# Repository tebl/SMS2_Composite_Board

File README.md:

# Master System II Video Board

The Sega Master System II was launched in a newer and updated styled case, unfortunately also missing quite a few features that were found in its earlier incarnation. Chief among them was the video output option, forcing you to rely on RF - an option being dropped on most newer TVs as well as looking rather dreadful on those that still have it.

This board aims to add composite or S-video back to your favourite mark II, making it usable today and giving you back the fun you had back in the day! Probably won't need a board like this since there aren't all that many connections and components in the first place, but tried it out and when doing more than one system conversion I figured there was enough of a wire mess to deal with so a small board made sense.

Board is sectioned off so that only the top section is used for composite video, so if you don't intend to use s-video you can save a bunch of wireing and skip these components. Note that it is important to pick power and ground connections that are close to the CXA1145P chip, but not every source is equal - while both pin 12 and 19 are power pins, using 12 as VCC for the circuit will result in glitches on the system (mine goes B/W and flashes purple from time to time) so stick with 19 for that. Don't do what I did, count twice and solder it right the first time. See images below for inspiration!

The extra wires going to the 64-pin chip (leg is cut to make this work) is used in combination with the switch to toggle between 50 and 60Hz. In PAL consoles this is used to let us play the game at full speed, just like the japanese and american consoles. At this point I consider the stock 50Hz setting "easy"-mode!

# Schematic
The supplied KiCad files should be sufficient as both a schematic and as a  starting point for ordering PCBs (basically you could just zip the contents of the export folder and upload that on a fabrication site), the schematic is also available in [PDF-format](https://github.com/tebl/SMS2_Composite_Board/raw/master/export/Master%20System%20II%20Video%20Board.pdf) and this is what you'll need to print and work your way through this things don't work as expected after assembly.

# BOM
Most parts should be easy to get a hold of from your favourite local electronic component shop, but given that I don't have access to such shops where I live so everything was based on whatever I could get cheapest from ebay/AliExpress (free shipping, plan on usually waiting 3-4 weeks though). The list below should be everything you'll need in addition to a workable soldering iron and some 60/40 soldering tin. For superior results, consider using shielded wire when doing the install!

Components in parenthesis are those needed extra for the S-video parts, so feel free to only install the parts needed for your own setup.

| Reference    | Item                                  | Count |
| ------------ | ------------------------------------- | ----- |
| PCB          | Fabricate using Gerber files ([order](https://www.pcbway.com/project/shareproject/Sega_Master_System_II_Composite_Video_Board.html=88707))  |     1 |
| C1           | 470uf electrolytic capacitor          |     1 |
| R1           | 150 ohm resistor                      |   (1) | 
| R2,R4        | 75 ohm resistor                       |     2 |
| R3           | 33 ohm resistor                       |   (1) |
| Q1,Q2        | 2N3904 transistor (TO-92)             | 1 (1) |

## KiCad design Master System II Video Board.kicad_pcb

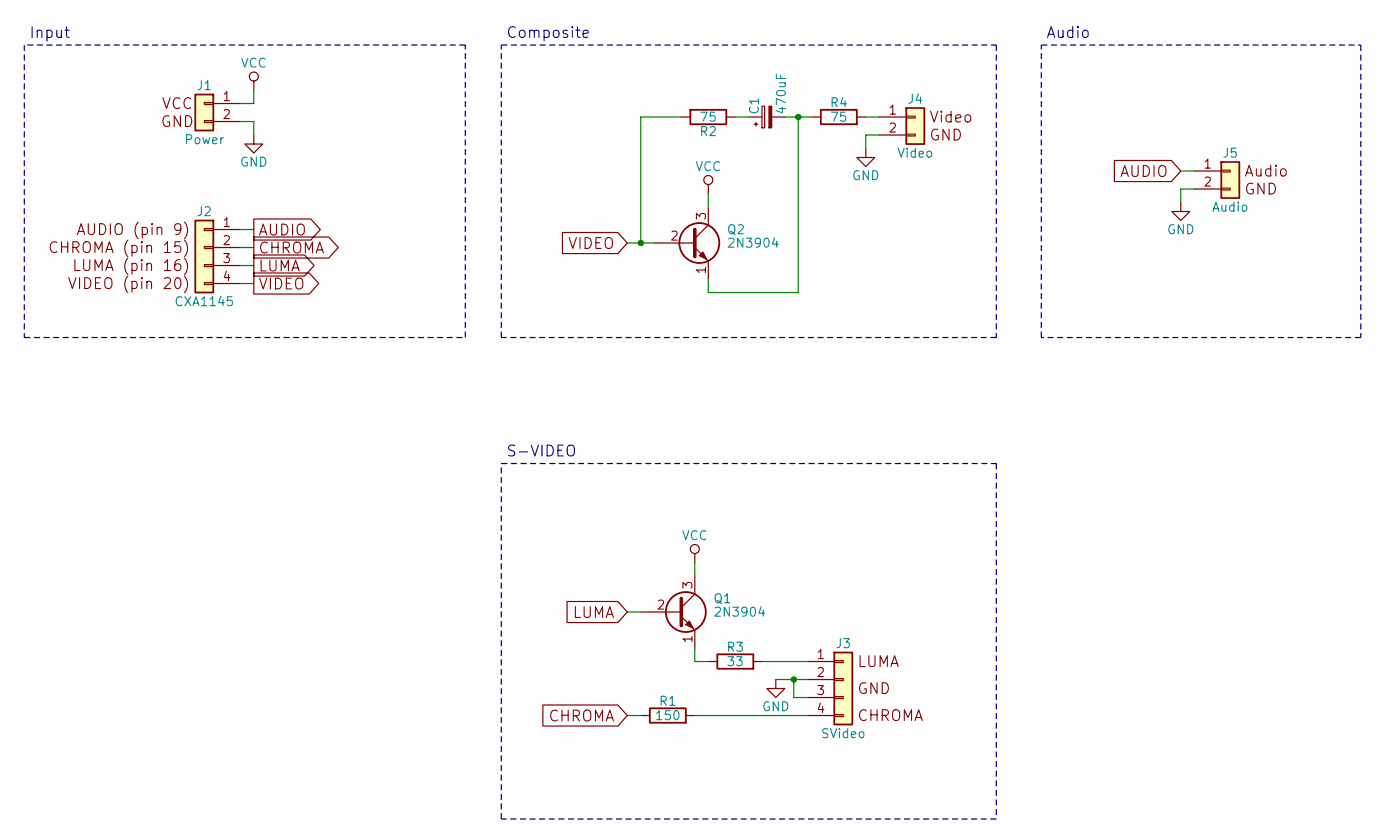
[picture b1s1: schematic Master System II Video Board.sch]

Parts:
C1: 470uF; CP_Radial_D5.0mm_P2.50mm
J1: Power; Pin_Header_Straight_1x02_Pitch2.54mm
J2: CXA1145; Pin_Header_Straight_1x04_Pitch2.54mm
J3: SVideo; Pin_Header_Straight_1x04_Pitch2.54mm
J4: Video; Pin_Header_Straight_1x02_Pitch2.54mm
J5: Audio; Pin_Header_Straight_1x02_Pitch2.54mm
Q1, Q2: 2N3904; TO-92_Inline_Wide
R1: 150; R_Axial_DIN0207_L6.3mm_D2.5mm_P10.16mm_Horizontal
R2, R4: 75; R_Axial_DIN0207_L6.3mm_D2.5mm_P10.16mm_Horizontal
R3: 33; R_Axial_DIN0207_L6.3mm_D2.5mm_P10.16mm_Horizontal

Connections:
AUDIO: J2.1 (AUD), J5.1 (Audio)
CHROMA: J2.2 (CHROMA), R1.1
GND: J1.2 (GND), J3.2 (GND), J3.3 (GND), J4.2 (GND), J5.2 (GND)
LUMA: J2.3 (LUMA), Q1.2 (B)
unnamed: C1.1, R2.1
unnamed: C1.2, Q2.1 (E), R4.1
unnamed: J3.1 (LUMA), R3.2
unnamed: J3.4 (CHROMA), R1.2
unnamed: J4.1 (Video), R4.2
unnamed: Q1.1 (E), R3.1
VCC: J1.1 (VCC), Q1.3 (C), Q2.3 (C)
VIDEO: J2.4 (VID), Q2.2 (B), R2.2

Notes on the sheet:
S-VIDEO
Composite
Input
Audio

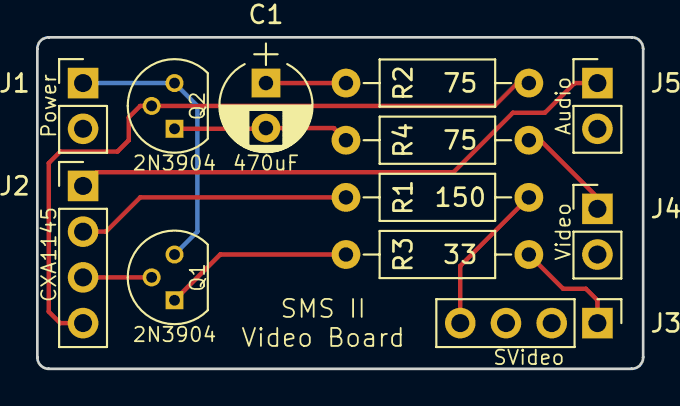
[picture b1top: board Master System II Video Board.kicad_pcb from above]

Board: 2 copper layers, 33.7 x 18.4 mm, 12 parts (0 on the bottom side), 12 nets.

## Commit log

2019-05-31 Basic layout done
2019-05-31 Gerber export
2019-06-15 Added gallery images
2019-06-15 Not those pictures!
2019-06-15 Added pictures to
2019-06-15 Added note about 50/60Hz switch shown in pictures
2019-06-17 Fixed order url
